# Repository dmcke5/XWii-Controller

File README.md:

# XWii Controller
An Xbox One style controller with a Wii U layout!

The Wii U gamepad layout is a fan-favourite for many gamers yet it is rarely used in the current generation of controllers. This open source project brings the Wii-U layout back but in a shape more akin to an Xbox controller and provides you with a cool piece of tech that you can be proud to say you built yourself!

Features:
- Wii-U controller layout
- Hall Effect Joysticks
- Hall Effect Triggers
- Rumble
- Xinput Compatible
- RGB Status indicator home button

For now, this controller is wired only but I plan to add a wireless version of the design at some point in the future!

# Print Orientation

If you're printing the housing at home on an FDM printer here's some tips to get the best finish possible!

#### Front Housing

Stand the front housing on its top edge and lean it forward 45 degrees. Enable supports for surfaces over 55 degrees and use a raft to ensure good adhesion to the bed. Ensure Z seam is on the inside! Only minimal supports should be generated, just to support the bottom of the button holes. If you're using a bed-slinger, orient your part so that it runs with the direction your bed moves to reduce wobble.

#### Rear Housing

Stand the rear housing on its top edge and lean it back 30 degrees. Enable supports for surfaces over 55 degrees and use a raft to ensure good adhesion to the bed. Ensure Z seam is on the inside! Some supports will be generated on the inside but none are in contact with critical surfaces making cleanup relatively easy. Same as the front, ensure orientation matches your bed movements for bed slinger printers!

#### Shoulder Buttons

Shoulder buttons should be printed flat on the bed, to ensure the spring is working with the layers rather than against them. Enable supports so the top edge of the buttons aren't left hanging.

#### Trigger Buttons

Stand trigger buttons on their end and rotate forward 30 degrees. Enable supports for surfaces over 55 degrees and enable raft. Supports should be generated in the holes and for the magnet mount only leaving very little cleanup required.

# Bill of materials

#### PCB's

1x Front PCB (Must use ENIG finish!)

1x Rear PCB

#### 3D Printing

1x Controller Housing Top

1x Controller Housing Bottom

1x LHS Shoulder Button

1x LHS Trigger

1x RHS Shoulder Button

1x RHS Trigger

#### Purchase

1x Switch lite button set - https://www.aliexpress.com/item/1005007266706005.html

1x Switch lite membrane set - https://www.aliexpress.com/item/1005004544710872.html

2x PS5 Hall sensor joysticks - https://www.aliexpress.com/item/1005007688806322.html

1x Xbox rumble motor (pair) - https://www.aliexpress.com/item/1005002877455453.html

2x PS4/5 Trigger Springs - https://www.aliexpress.com/item/1005005844578554.html

2x 3x1mm Neodymium Magnets - https://www.aliexpress.com/item/1005006619263188.html

1x 6028 RGB LED - https://www.aliexpress.com/item/1005003719602946.html

1x WS2811 IC - https://www.aliexpress.com/item/32844615804.html

1x USB Data Cable (End will be removed so only need to ensure it has the correct end for your device on one end of the cable)

#### Hardware

5x M3x5x5 Threaded Inserts

2x M2x3.2x3 Threaded Inserts

3x M2x3.2x4 Threaded Inserts

5x M3x8 SHCS Screws

6x M2x4 SHCS Screws

# PCB Assembly

#### Front PCB:

Follow the diagram below for locations of components. Pay close attention to orientation of parts U1, Y1, U7 and D1 as they can be fitted in the wrong direction and cause damage. Align marks on all these components with the alignment marks on the PCB.

#### Rear PCB:

Follow the diagram below for locations of components. Fit joysticks to opposite side of PCB.

# Software

You will need to install these libraries to be able to compile the code:

XInput: https://github.com/dmadison/ArduinoXInput

FastLED: https://github.com/FastLED/FastLED

Then simply compile and upload to your controller using the Leonardo w/xinput board option. Please note, once the code is uploaded you will need to re-flash the bootloader to be able to upload code again due to a limitation in the way the xinput library works.

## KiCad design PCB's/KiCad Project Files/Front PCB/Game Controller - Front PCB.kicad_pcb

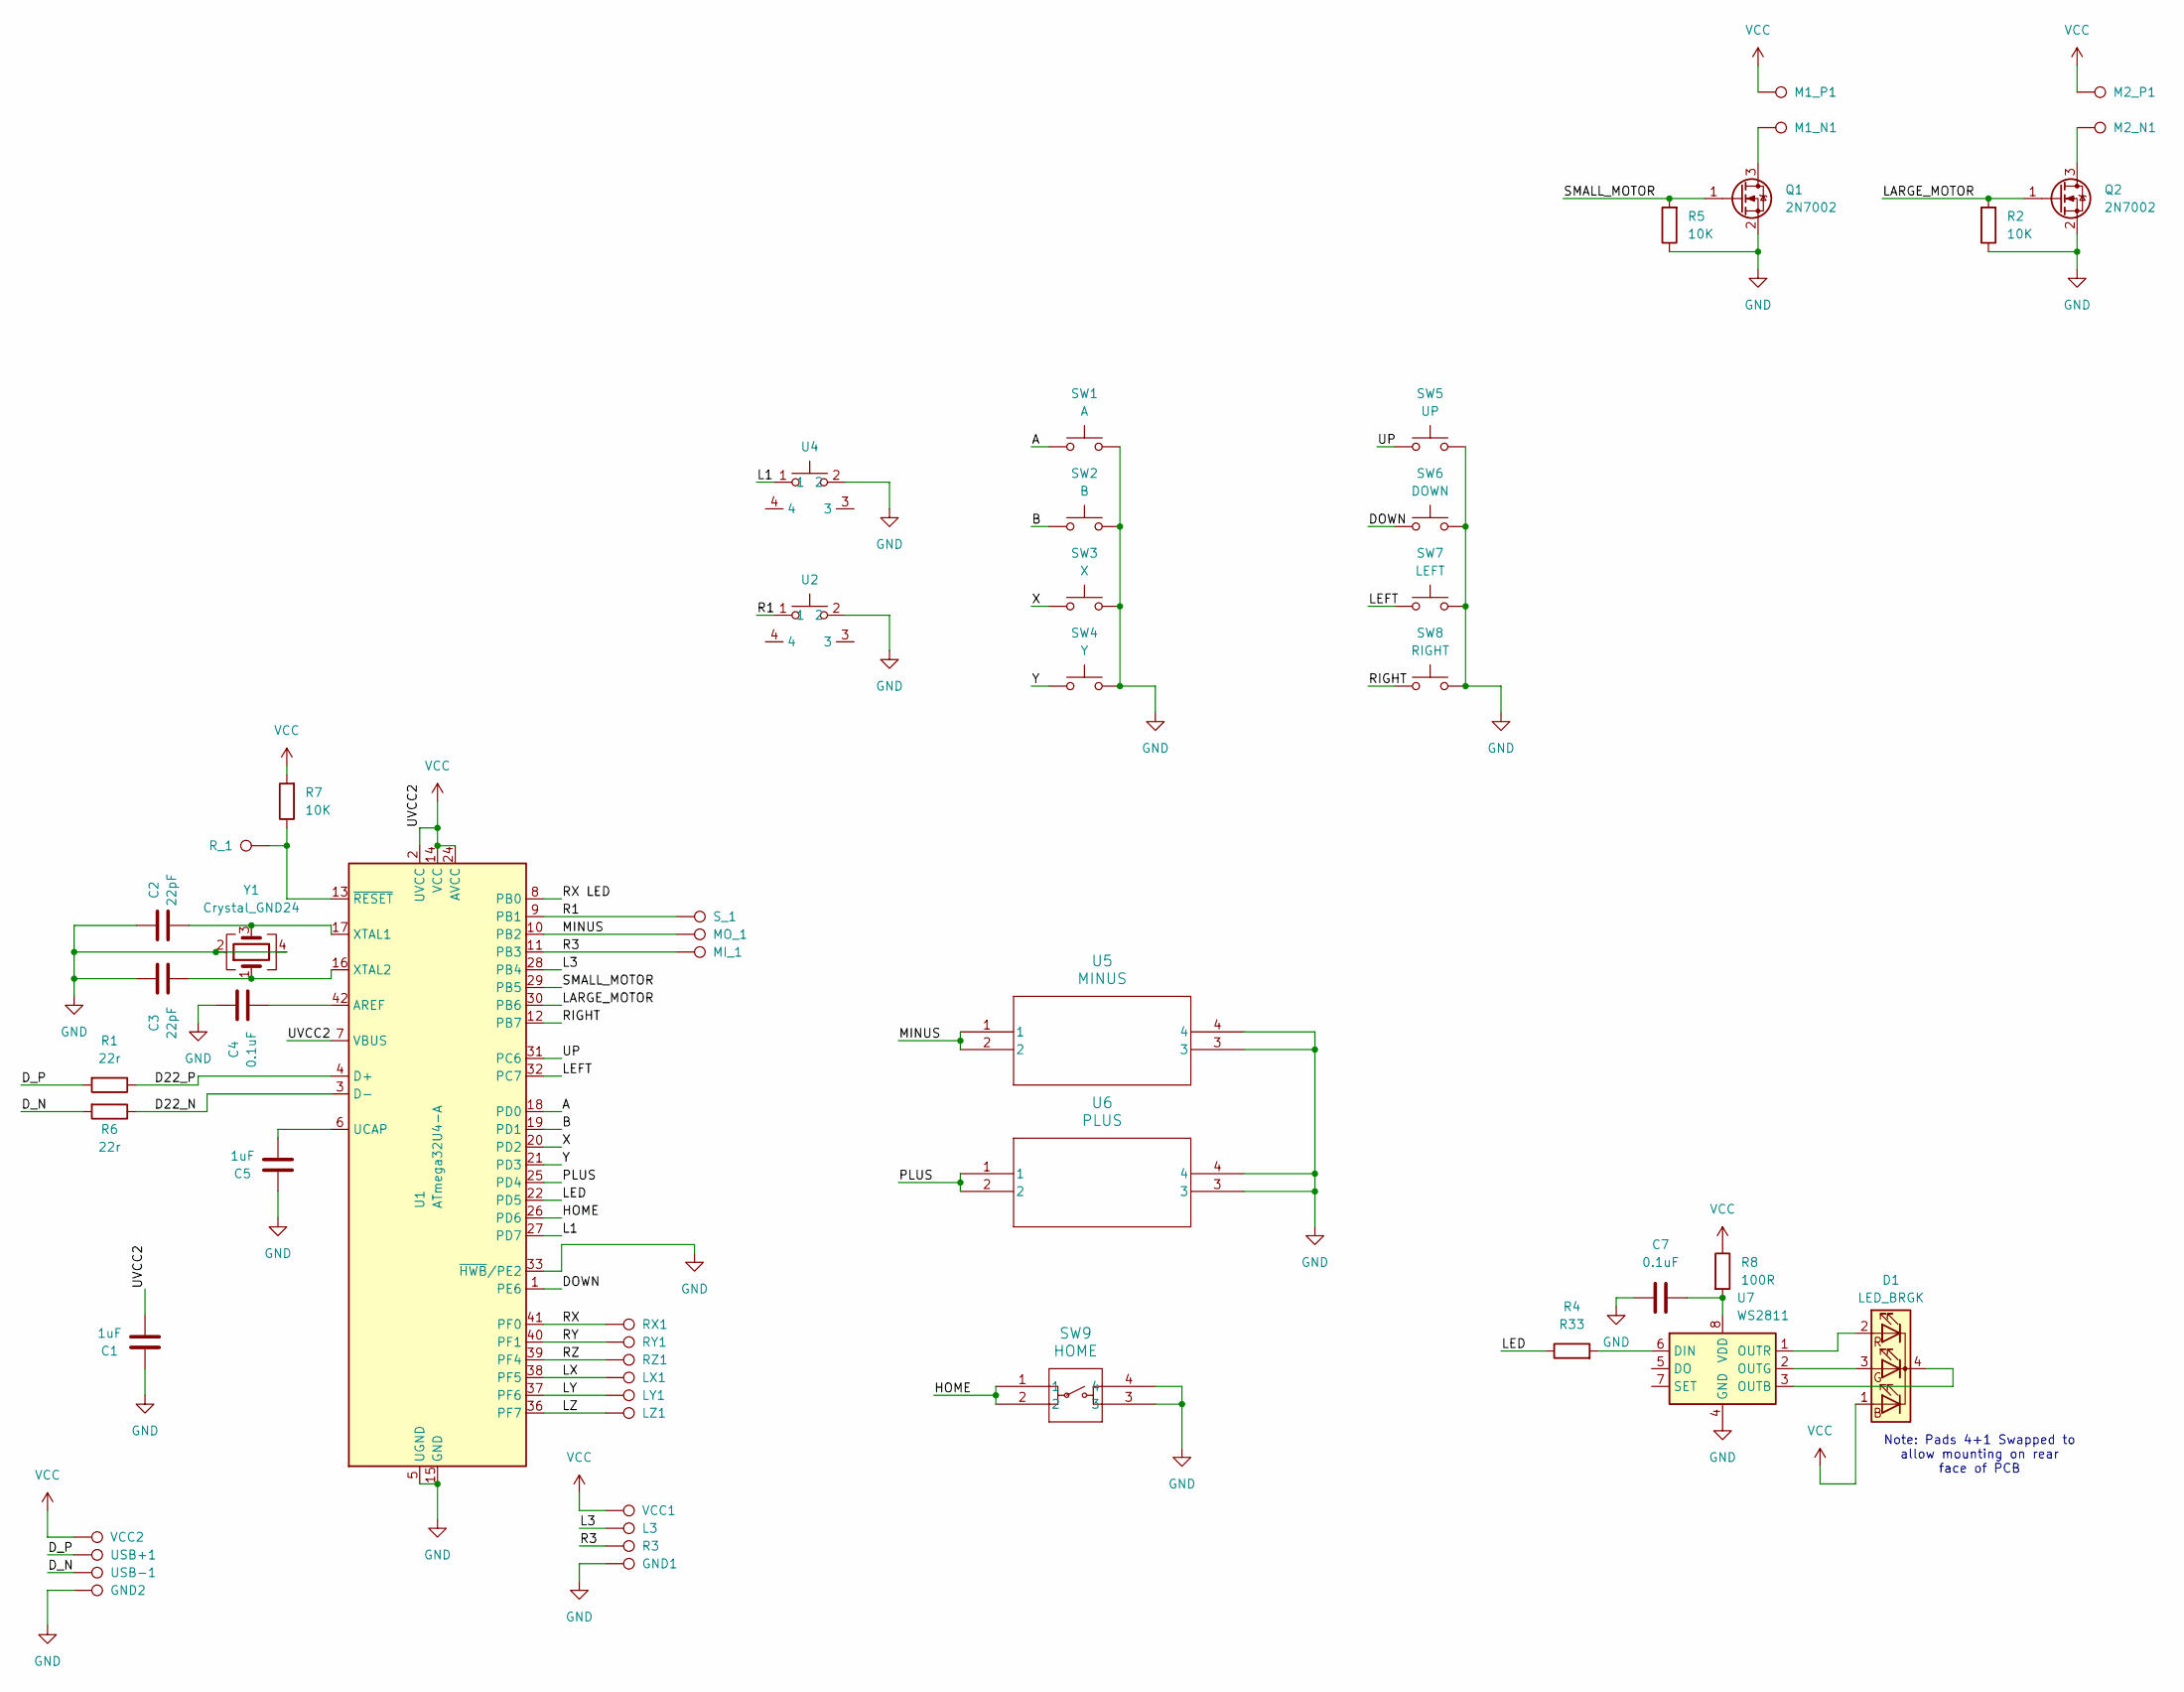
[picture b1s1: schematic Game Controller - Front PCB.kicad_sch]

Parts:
C1, C5: 1uF; C_0603_1608Metric_Pad1.08x0.95mm_HandSolder
C2, C3: 22pF; C_0603_1608Metric_Pad1.08x0.95mm_HandSolder
C4, C7: 0.1uF; C_0603_1608Metric_Pad1.08x0.95mm_HandSolder
D1: LED_BRGK; LED_T36K3BGR-05D000121U1930
GND1: GND; TestPoint_Pad_D1.0mm
GND2: GND; TestPoint_THTPad_D2.0mm_Drill1.0mm
L3: L3; TestPoint_Pad_D1.0mm
LX1: LX; TestPoint_Pad_D1.0mm
LY1: LY; TestPoint_Pad_D1.0mm
LZ1: LZ; TestPoint_Pad_D1.0mm
M1_N1, M1_P1, M2_N1, M2_P1: MOSI; TestPoint_THTPad_D2.0mm_Drill1.0mm
MI_1: MISO; TestPoint_Pad_D1.5mm
MO_1: MOSI; TestPoint_Pad_D1.5mm
Q1, Q2: 2N7002; SOT-23
R1, R6: 22r; R_0603_1608Metric_Pad0.98x0.95mm_HandSolder
R2, R5, R7: 10K; R_0603_1608Metric_Pad0.98x0.95mm_HandSolder
R3: R3; TestPoint_Pad_D1.0mm
R4: R33; R_0603_1608Metric_Pad0.98x0.95mm_HandSolder
R8: 100R; R_0603_1608Metric_Pad0.98x0.95mm_HandSolder
RX1: RX; TestPoint_Pad_D1.0mm
RY1: RY; TestPoint_Pad_D1.0mm
RZ1: RZ; TestPoint_Pad_D1.0mm
R_1: RESET; TestPoint_Pad_D1.5mm
SW1: A; Membrane Button Small
SW2: B; Membrane Button Small
SW3: X; Membrane Button Small
SW4: Y; Membrane Button Small
SW5: UP; Membrane Button Small
SW6: DOWN; Membrane Button Small
SW7: LEFT; Membrane Button Small
SW8: RIGHT; Membrane Button Small
SW9: HOME; TL3315NF100Q_EWI
S_1: SCK; TestPoint_Pad_D1.5mm
U1: ATmega32U4-A; TQFP-44_10x10mm_P0.8mm
U2, U4: MJTP1117
U5: MINUS; SMT_FS
U6: PLUS; SMT_FS
U7: WS2811; SOP-8_3.9x4.9mm_P1.27mm
USB+1: USB+; TestPoint_THTPad_D2.0mm_Drill1.0mm
USB-1: USB-; TestPoint_THTPad_D2.0mm_Drill1.0mm
VCC1: VCC; TestPoint_Pad_D1.0mm
VCC2: VCC; TestPoint_THTPad_D2.0mm_Drill1.0mm
Y1: Crystal_GND24; Crystal_SMD_5032-4Pin_5.0x3.2mm

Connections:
/A: SW1.1, U1.18 (PD0)
/B: SW2.1, U1.19 (PD1)
/D22_N: R6.1, U1.3 (D-)
/D22_P: R1.1, U1.4 (D+)
/DOWN: SW6.1, U1.1 (PE6)
/D_N: R6.2, USB-1.1
/D_P: R1.2, USB+1.1
/HOME: SW9.1, SW9.2, U1.26 (PD6)
/L1: U1.27 (PD7), U4.1
/L3: L3.1, U1.28 (PB4)
/LARGE_MOTOR: Q2.1 (G), R2.2, U1.30 (PB6)
/LED: R4.1, U1.22 (PD5)
/LEFT: SW7.1, U1.32 (PC7)
/LX: LX1.1, U1.38 (PF5)
/LY: LY1.1, U1.37 (PF6)
/LZ: LZ1.1, U1.36 (PF7)
/MINUS: MO_1.1, U1.10 (PB2), U5.1, U5.2
/PLUS: U1.25 (PD4), U6.1, U6.2
/R1: S_1.1, U1.9 (PB1), U2.1
/R3: MI_1.1, R3.1, U1.11 (PB3)
/RIGHT: SW8.1, U1.12 (PB7)
/RX: RX1.1, U1.41 (PF0)
/RX LED: U1.8 (PB0)
/RY: RY1.1, U1.40 (PF1)
/RZ: RZ1.1, U1.39 (PF4)
/SMALL_MOTOR: Q1.1 (G), R5.2, U1.29 (PB5)
/UP: SW5.1, U1.31 (PC6)
/X: SW3.1, U1.20 (PD2)
/Y: SW4.1, U1.21 (PD3)
GND: C1.1, C2.1, C3.1, C4.1, C5.1, C7.1, GND1.1, GND2.1, Q1.2 (S), Q2.2 (S), R2.1, R5.1, SW1.2, SW2.2, SW3.2, SW4.2, SW5.2, SW6.2, SW7.2, SW8.2, SW9.3, SW9.4, U1.5 (UGND), U1.15 (GND), U1.23 (GND), U1.33 (~HWB/PE2), U1.35 (GND), U1.43 (GND), U2.2, U4.2, U5.3, U5.4, U6.3, U6.4, U7.4 (GND), Y1.2, Y1.4
unnamed: D1.3 (GA), U7.2 (OUTG)
unnamed: D1.4 (K), U7.3 (OUTB)
unnamed: D1.2 (RA), U7.1 (OUTR)
unnamed: M1_N1.1, Q1.3 (D)
unnamed: M2_N1.1, Q2.3 (D)
unnamed: C4.2, U1.42 (AREF)
unnamed: C5.2, U1.6 (UCAP)
unnamed: C2.2, U1.17 (XTAL1), Y1.3
unnamed: C3.2, U1.16 (XTAL2), Y1.1
unnamed: R7.1, R_1.1, U1.13 (~RESET)
unnamed: R4.2, U7.6 (DIN)
unnamed: C7.2, R8.2, U7.8 (VDD)
VCC: C1.2, D1.1 (BA), M1_P1.1, M2_P1.1, R7.2, R8.1, U1.2 (UVCC), U1.7 (VBUS), U1.14 (VCC), U1.24 (AVCC), U1.34 (VCC), U1.44 (AVCC), VCC1.1, VCC2.1

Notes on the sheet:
Note: Pads 4+1 Swapped to allow mounting on rear face of PCB

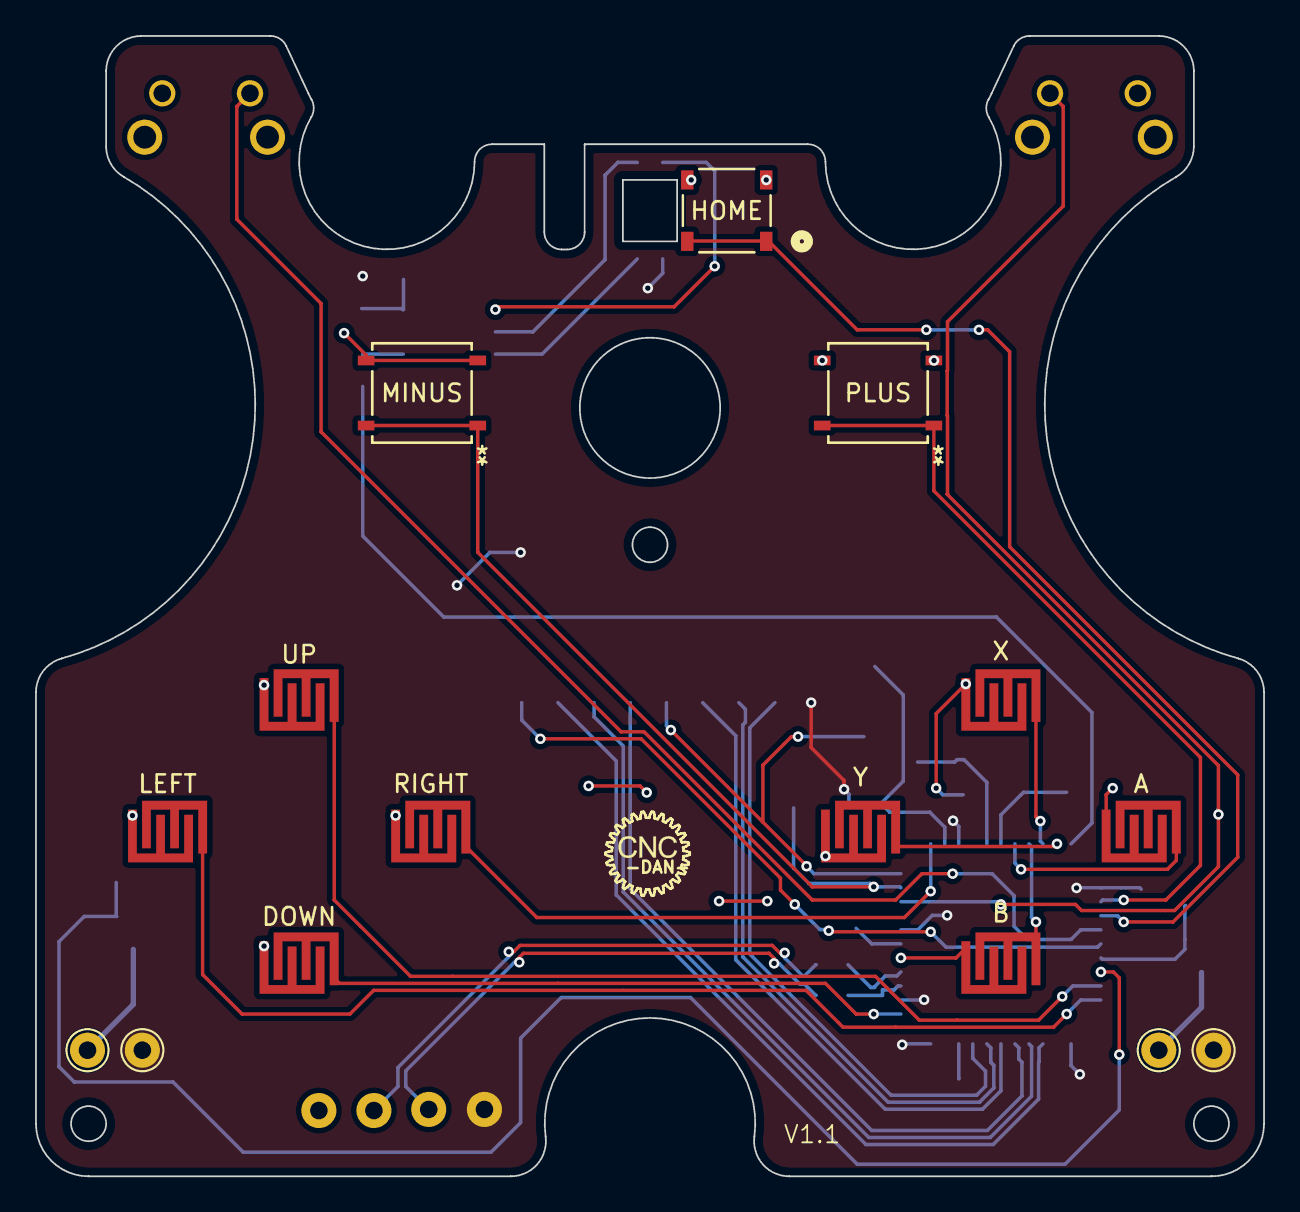
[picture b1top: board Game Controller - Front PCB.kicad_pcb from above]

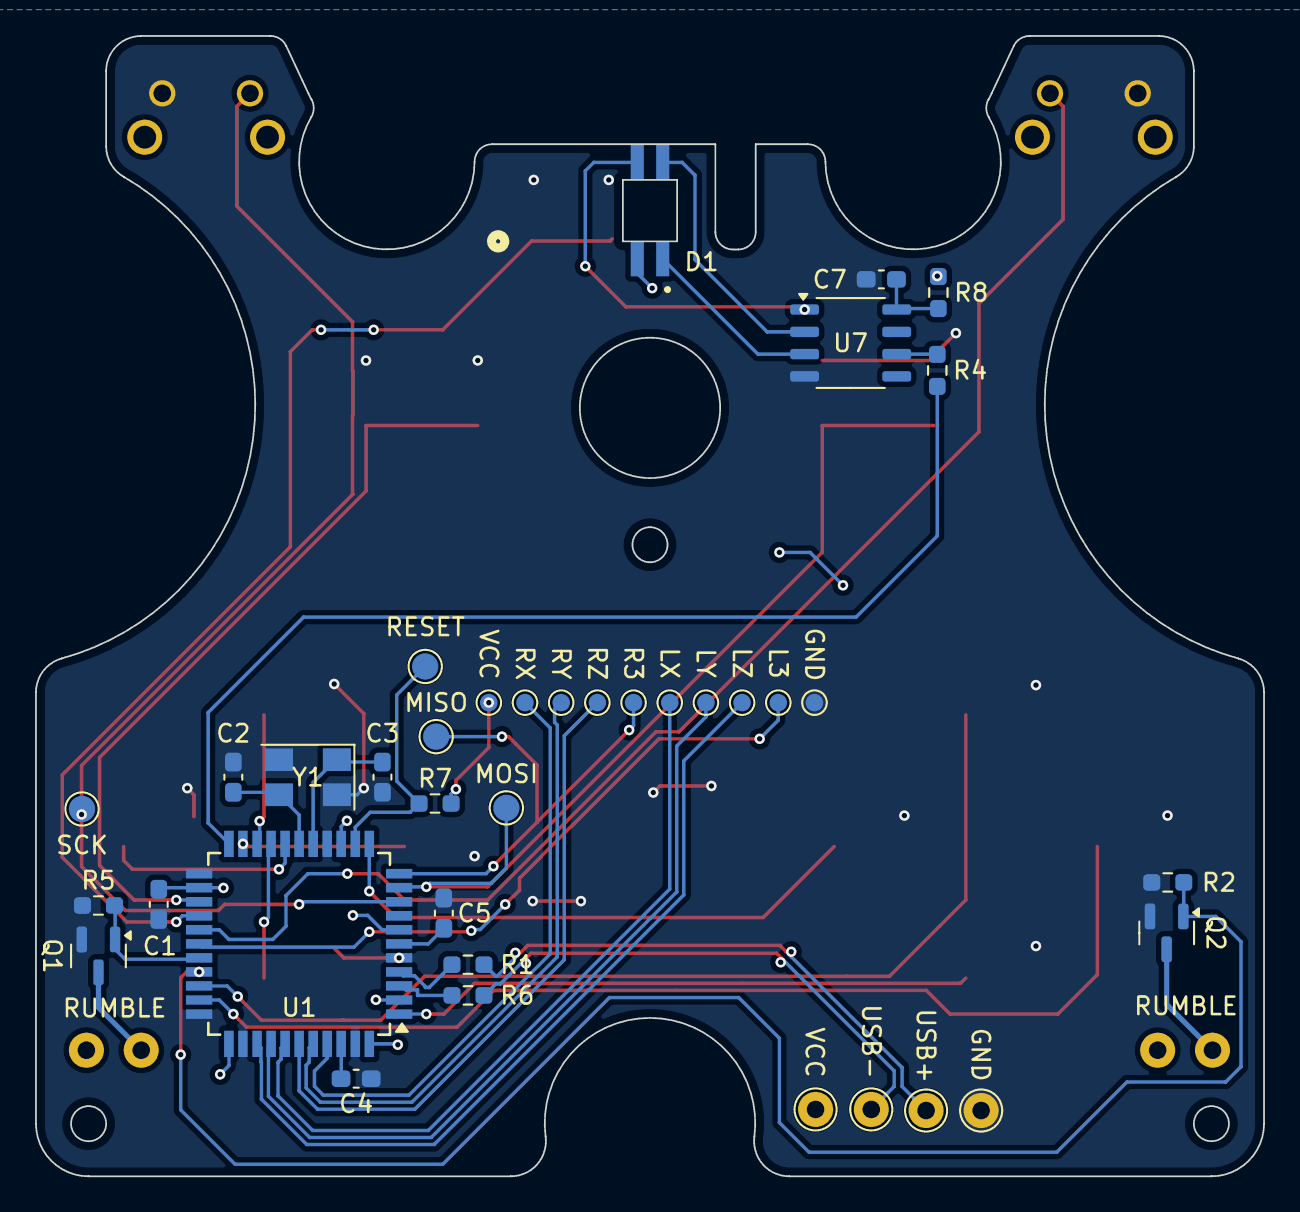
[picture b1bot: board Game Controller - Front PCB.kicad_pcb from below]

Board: 2 copper layers, 70.0 x 65.0 mm, 54 parts (38 on the bottom side), 42 nets.

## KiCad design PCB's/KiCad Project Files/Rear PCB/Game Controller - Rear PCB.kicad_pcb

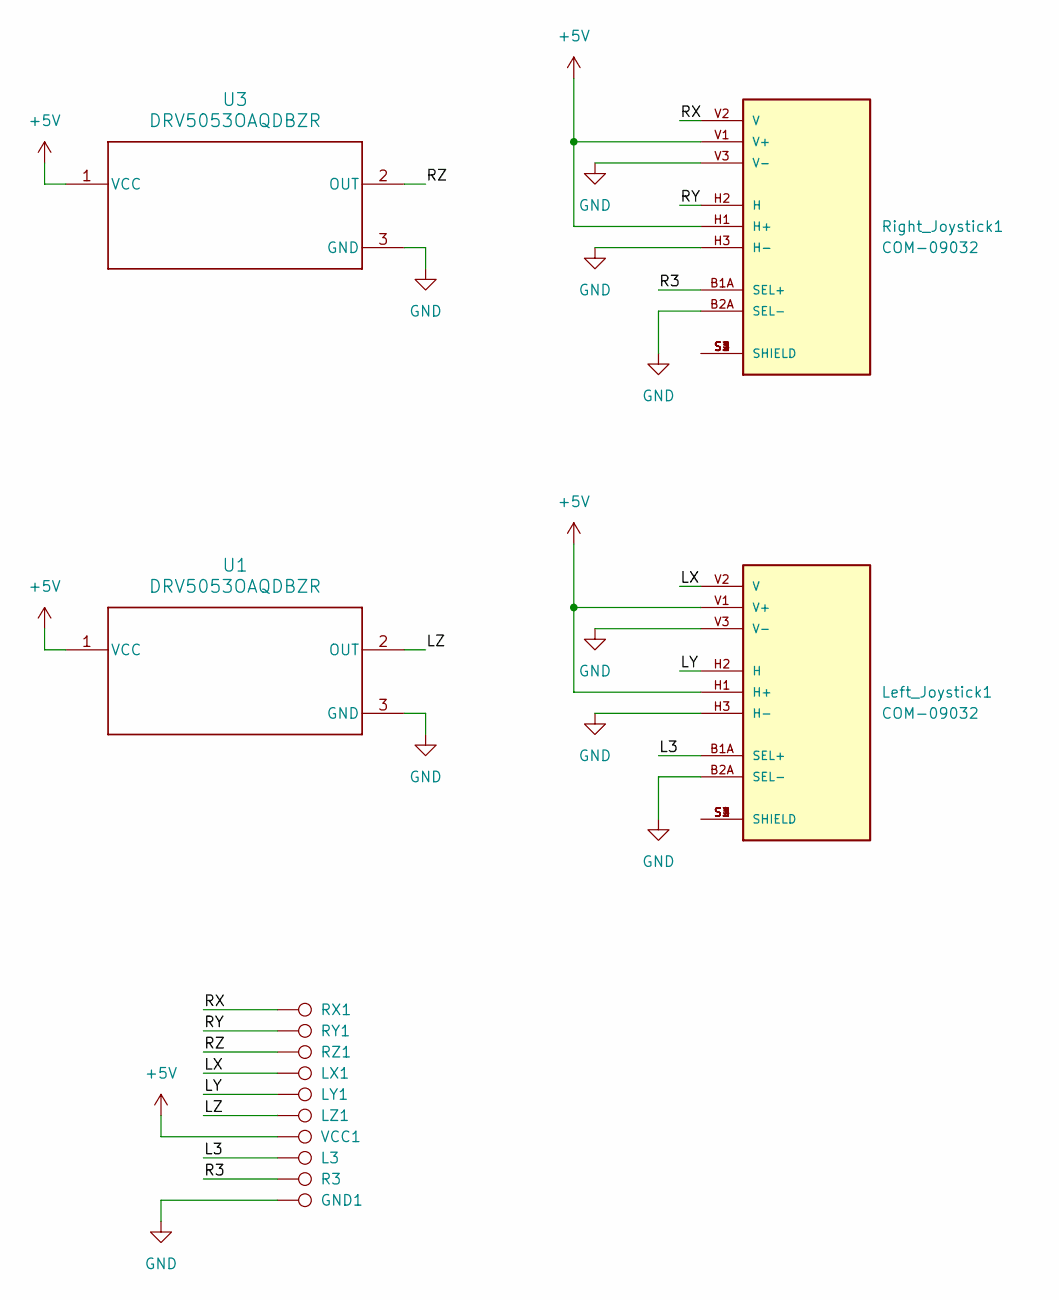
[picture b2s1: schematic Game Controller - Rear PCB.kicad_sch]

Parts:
GND1: GND; TestPoint_Pad_D1.0mm
L3: L3; TestPoint_Pad_D1.0mm
LX1: LX; TestPoint_Pad_D1.0mm
LY1: LY; TestPoint_Pad_D1.0mm
LZ1: LZ; TestPoint_Pad_D1.0mm
Left_Joystick1: COM-09032; PS5 Joystick; PARTREV N/A
R3: R3; TestPoint_Pad_D1.0mm
RX1: RX; TestPoint_Pad_D1.0mm
RY1: RY; TestPoint_Pad_D1.0mm
RZ1: RZ; TestPoint_Pad_D1.0mm
Right_Joystick1: COM-09032; PS5 Joystick; PARTREV N/A
U1, U3: DRV5053OAQDBZR; DBZ0003A_N
VCC1: VCC; TestPoint_Pad_D1.0mm

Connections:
+5V: Left_Joystick1.H1 (H+), Left_Joystick1.V1 (V+), Right_Joystick1.H1 (H+), Right_Joystick1.V1 (V+), U1.1 (VCC), U3.1 (VCC), VCC1.1
/L3: L3.1, Left_Joystick1.B1A (SEL+)
/LX: LX1.1, Left_Joystick1.V2 (V)
/LY: LY1.1, Left_Joystick1.H2 (H)
/LZ: LZ1.1, U1.2 (OUT)
/R3: R3.1, Right_Joystick1.B1A (SEL+)
/RX: RX1.1, Right_Joystick1.V2 (V)
/RY: RY1.1, Right_Joystick1.H2 (H)
/RZ: RZ1.1, U3.2 (OUT)
GND: GND1.1, Left_Joystick1.B2A (SEL-), Left_Joystick1.H3 (H-), Left_Joystick1.V3 (V-), Right_Joystick1.B2A (SEL-), Right_Joystick1.H3 (H-), Right_Joystick1.V3 (V-), U1.3 (GND), U3.3 (GND)
unnamed: Left_Joystick1.S1 (SHIELD), Left_Joystick1.S2 (SHIELD), Left_Joystick1.S3 (SHIELD), Left_Joystick1.S4 (SHIELD)
unnamed: Right_Joystick1.S1 (SHIELD), Right_Joystick1.S2 (SHIELD), Right_Joystick1.S3 (SHIELD), Right_Joystick1.S4 (SHIELD)

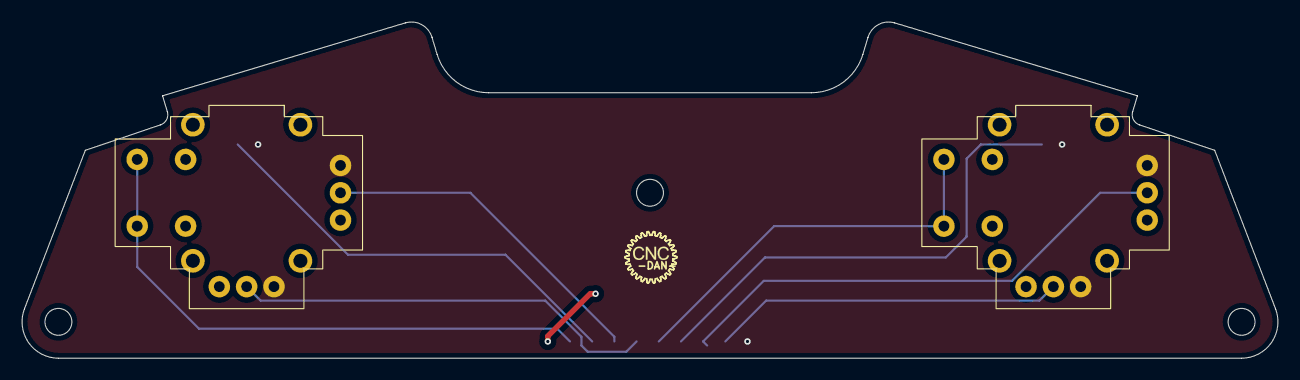
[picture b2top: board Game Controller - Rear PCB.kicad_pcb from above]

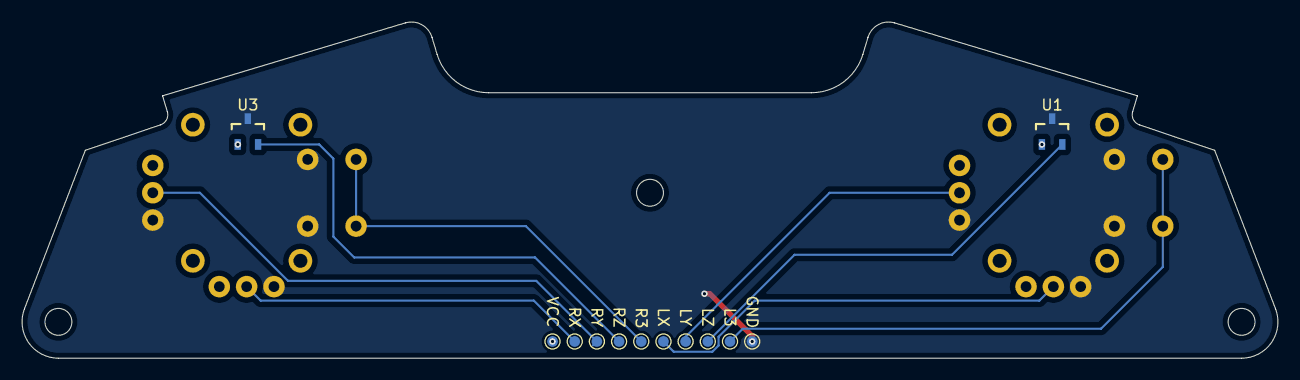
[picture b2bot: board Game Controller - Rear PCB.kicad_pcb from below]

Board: 2 copper layers, 116.8 x 31.3 mm, 14 parts (12 on the bottom side), 12 nets.

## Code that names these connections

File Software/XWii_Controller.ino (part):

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
//Controller IO setup
int buttonCount = 15;                   //Number of buttons connected
byte buttonPins[15] = {15,16, 14, 8, 11, 5, 13, 3, 2, 0, 1, 4, 12, 6, 7}; //R1, Minus, R3, L3, Right, Up, Left, A, B, X, Y, Plus, Home, L1, Down,  

#define leftZ A0
#define leftX A2
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
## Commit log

2024-11-29 Create Licence
2024-11-29 Add 3D Models
2024-11-29 Added PCB's and Title Image
2024-11-29 Updates to readme and print orientation suggestions
2024-11-29 Update naming convention on picture
2024-11-29 More naming convention updates
2024-11-29 Added Assembly Drawing
2024-12-19 Added Front PCB BOM and updated front PCB Gerbers to V1.1
2024-12-19 Updated file names
2024-12-19 Added Rear PCB BOM
2024-12-19 Updated front PCB drawing and kicad project files
2024-12-19 Update Controller Housing to suit cheap replacement rumble motors
2024-12-19 Added blank front housing for custom layouts
2024-12-20 Added items to purchase list
2024-12-21 Update README.md
    Renamed Project
2024-12-21 Update README.md
    Updated link for rumble motors
2024-12-21 Update README.md
    Updated BOM
2024-12-21 Create Software Folder
2024-12-21 Added Rev1.0 of XWii Controller Software
2025-01-04 Added automatic detection for inverted magnet orientation during calibration
2025-01-04 Added quiet PWM for rumble motors
2025-02-05 Updated Front PCB BOM
    C7 was missing from BOM
2025-03-01 Update XWii_Controller.ino
    Fixed error in rumble code
